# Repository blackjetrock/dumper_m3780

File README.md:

# dumper_m3780
Dumper for the M3780 microcontroller family
===========================================

Uses Sean Riddle's dumper circuit, but with a RP Pico instead of the
PIC. I ported Sean's code over to the Pico but couldn't get reliable
reads, so I rewrote it to use a generic system of injecting instructions
and used a more elaborate scheme to get the data out of the device. This 
is very much a hacked together tool specifically built to dump a ROM. It's not
a finished product.

The TEST pin handling is the same as Sean's code, but I have code that
can inject a (preset, in arrays) sequence of code into the device. This
allowed me to debug my instruction extraction and come up with a method of 
reading ROM bytes reliably. As I still had issues with a value every
few hundred bytes I now read each byte in the ROM many times and only if
that block read gives the same value is it used as the ROM byte value.
If the values aren't the same then the block of reads is re-done 
until it is. This means it takes a while to read the ROM but the 
values are, I think, correct. I checked operation with the Boris chess
computer ROM and I got a dump that matched Sean's ecxept for the last
few bytes which are, I think, unused values.

I then dumped the ROM from a device out of an HP82143 printer. The Boris 
and HP dumps are in this repository.

The PCB is powered by the Pico USB, whih also has a menu system to drive the
code and get dumps.

At the moment the code always dumps 4K

ERRATA
======

V1.0 PCB
--------

This version of the PCB does not work unless you add level shifters 
between the Pico and the 4066 control lines. I added a couple of FETs
onto my PCB manually. If you don't do this then the PCB will
not work.

Here's the V1.0 PCB I used:

You can see a dc-dc converter module on the right, and the level shifters I wired in going from the 4066 
to the Pico on the left. The 40 pin IC is the M3780. the two LM317T circuits are on the right with their 
adjustment potentiometers.

Code
----
There's a menu system on the USB. Press 'h' to see the command list. To dump a ROM use 'u' then 'S' to dump the ROM. It takes a while as each byte
is read, when it's done the full dumpo is displayed. There's some problem that means that you need to select 'u'
before using 'S'. As this is a one or two use dumper, I'm not bothered by these wrinkles.

Links
=====

<pre>
Sean Riddle's site:                     https://seanriddle.com/
Forum thread:                           https://www.hpmuseum.org/forum/thread-20043.html
</pre>

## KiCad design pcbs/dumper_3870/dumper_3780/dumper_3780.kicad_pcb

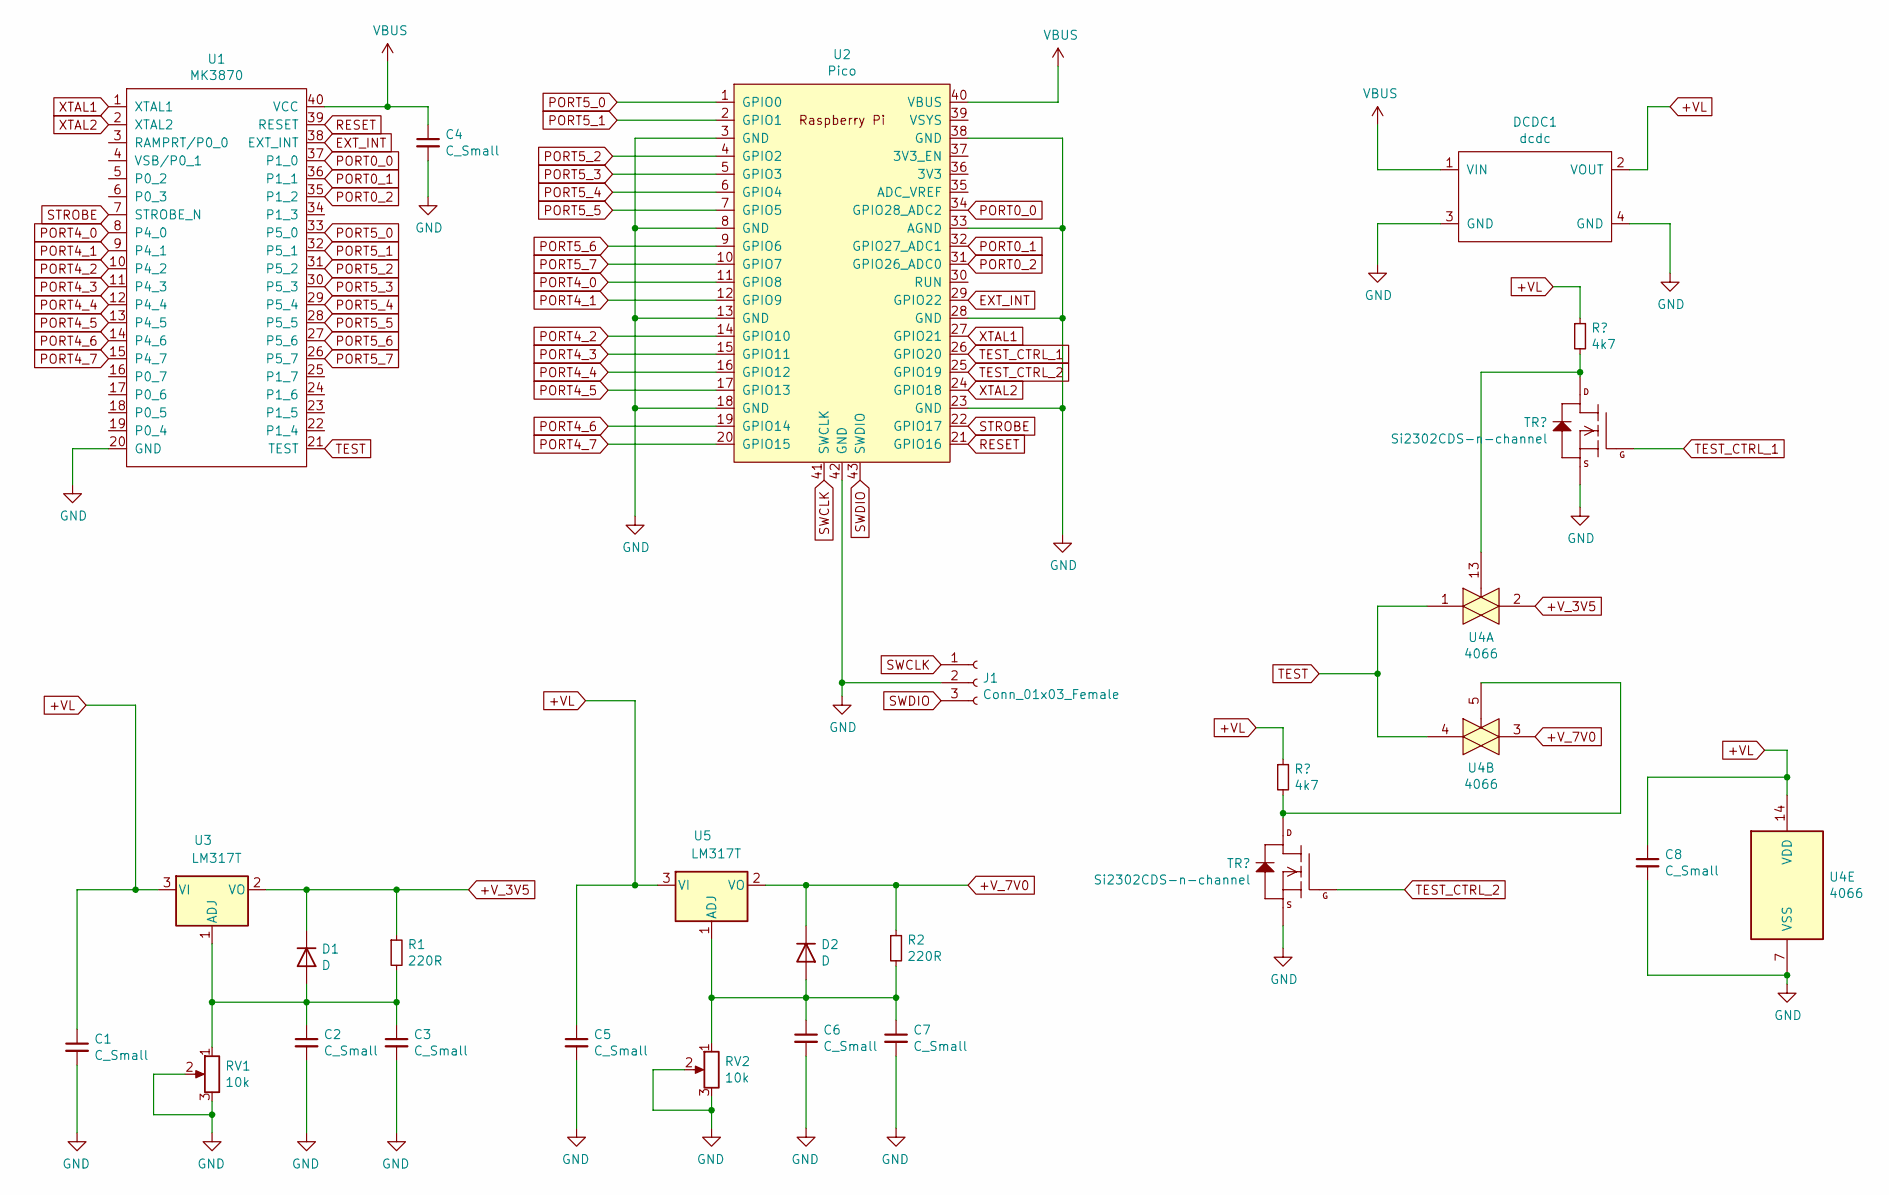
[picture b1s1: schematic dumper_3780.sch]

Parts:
C1, C2, C3, C4, C5, C6, C7, C8: C_Small; C_0805_2012Metric_Pad1.18x1.45mm_HandSolder
D1, D2: D; D_SOD-123
DCDC1: dcdc; PinSocket_1x04_P2.54mm_Vertical
J1: Conn_01x03_Female; PinSocket_1x03_P2.54mm_Vertical
R1, R2: 220R; R_0805_2012Metric_Pad1.20x1.40mm_HandSolder
RV1, RV2: 10k; Potentiometer_Bourns_3299W_Vertical
U1: MK3870; DIP-40_W15.24mm
U2: Pico; RPi_Pico_SMD_TH
U3, U5: LM317T; TO-220-3_Vertical
U4: 4066; SOIC-14_3.9x8.7mm_P1.27mm

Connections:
+VL: C1.1, C5.1, C8.1, DCDC1.2 (VOUT), U3.3 (VI), U4.14 (VDD), U5.3 (VI)
+V_3V5: D1.1 (K), R1.1, U3.2 (VO), U4.2
+V_7V0: D2.1 (K), R2.1, U4.3, U5.2 (VO)
EXT_INT: U1.38 (EXT_INT), U2.29 (GPIO22)
GND: C1.2, C2.2, C3.2, C4.2, C5.2, C6.2, C7.2, C8.2, DCDC1.3 (GND), DCDC1.4 (GND), J1.2, RV1.2, RV1.3, RV2.2, RV2.3, U1.20 (GND), U2.3 (GND), U2.8 (GND), U2.13 (GND), U2.18 (GND), U2.23 (GND), U2.28 (GND), U2.33 (AGND), U2.38 (GND), U2.42 (GND), U4.7 (VSS)
unnamed: C2.1, C3.1, D1.2 (A), R1.2, RV1.1, U3.1 (ADJ)
unnamed: C6.1, C7.1, D2.2 (A), R2.2, RV2.1, U5.1 (ADJ)
PORT0_0: U1.37 (P1_0), U2.34 (GPIO28_ADC2)
PORT0_1: U1.36 (P1_1), U2.32 (GPIO27_ADC1)
PORT0_2: U1.35 (P1_2), U2.31 (GPIO26_ADC0)
PORT4_0: U1.8 (P4_0), U2.11 (GPIO8)
PORT4_1: U1.9 (P4_1), U2.12 (GPIO9)
PORT4_2: U1.10 (P4_2), U2.14 (GPIO10)
PORT4_3: U1.11 (P4_3), U2.15 (GPIO11)
PORT4_4: U1.12 (P4_4), U2.16 (GPIO12)
PORT4_5: U1.13 (P4_5), U2.17 (GPIO13)
PORT4_6: U1.14 (P4_6), U2.19 (GPIO14)
PORT4_7: U1.15 (P4_7), U2.20 (GPIO15)
PORT5_0: U1.33 (P5_0), U2.1 (GPIO0)
PORT5_1: U1.32 (P5_1), U2.2 (GPIO1)
PORT5_2: U1.31 (P5_2), U2.4 (GPIO2)
PORT5_3: U1.30 (P5_3), U2.5 (GPIO3)
PORT5_4: U1.29 (P5_4), U2.6 (GPIO4)
PORT5_5: U1.28 (P5_5), U2.7 (GPIO5)
PORT5_6: U1.27 (P5_6), U2.9 (GPIO6)
PORT5_7: U1.26 (P5_7), U2.10 (GPIO7)
RESET: U1.39 (RESET), U2.21 (GPIO16)
STROBE: U1.7 (STROBE_N), U2.22 (GPIO17)
SWCLK: J1.1, U2.41 (SWCLK)
SWDIO: J1.3, U2.43 (SWDIO)
TEST: U1.21 (TEST), U4.1, U4.4
TEST_CTRL_1: U2.26 (GPIO20), U4.13
TEST_CTRL_2: U2.25 (GPIO19), U4.5
VBUS: C4.1, DCDC1.1 (VIN), U1.40 (VCC), U2.40 (VBUS)
XTAL1: U1.1 (XTAL1), U2.27 (GPIO21)
XTAL2: U1.2 (XTAL2), U2.24 (GPIO18)

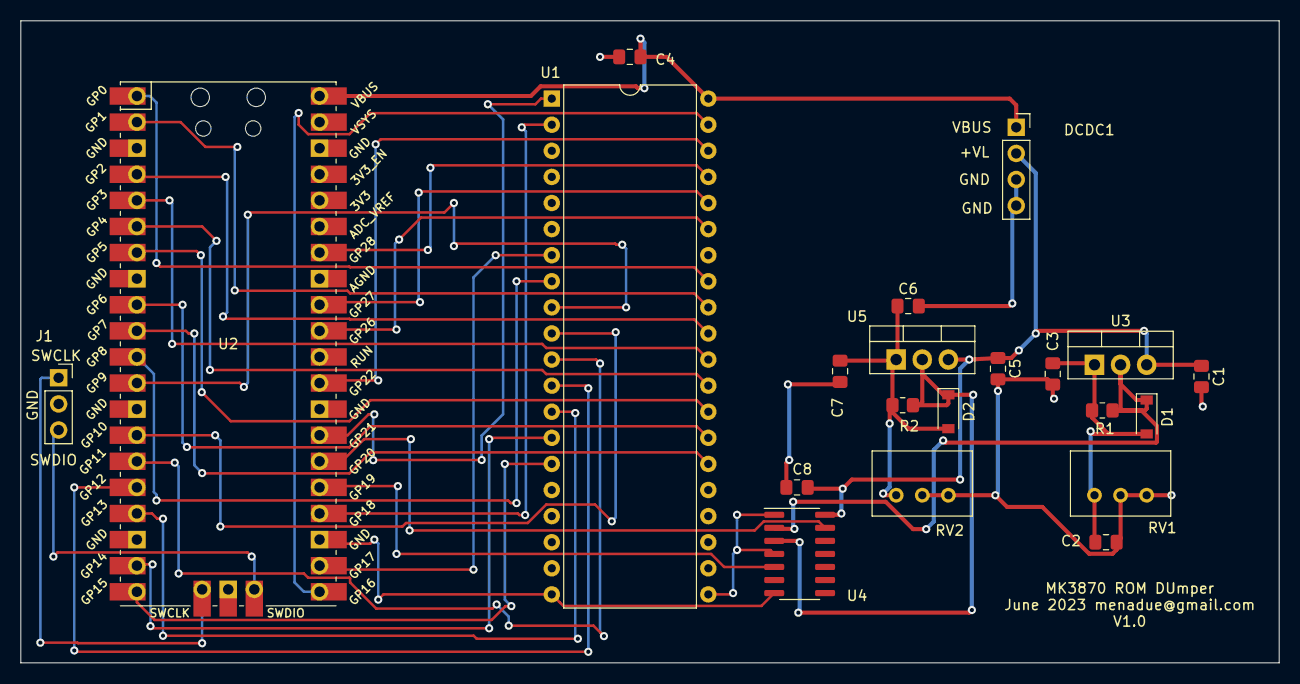
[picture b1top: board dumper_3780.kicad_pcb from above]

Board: 2 copper layers, 122.5 x 62.5 mm, 21 parts (0 on the bottom side), 36 nets.

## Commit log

2024-02-18 Added PDF of V2.0 shematic which has level shifters added. No PCb of this yet.
